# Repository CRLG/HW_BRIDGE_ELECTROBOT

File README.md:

# HW_BRIDGE_ELECTROBOT
Carte pont en H pour moteur DC

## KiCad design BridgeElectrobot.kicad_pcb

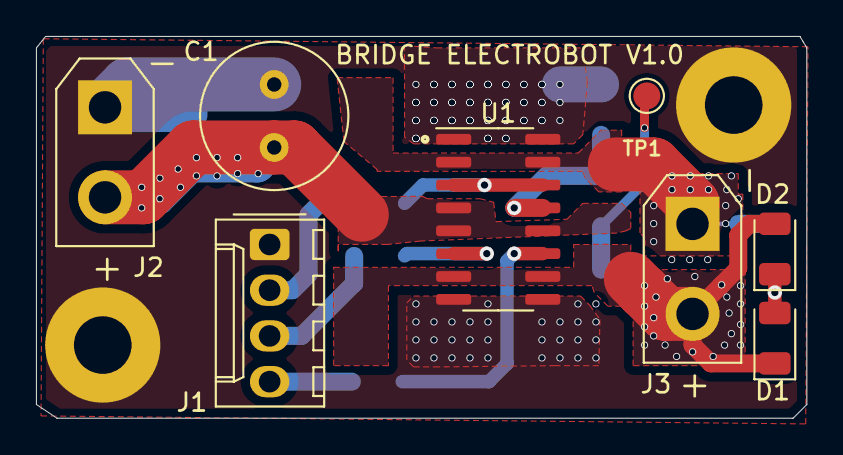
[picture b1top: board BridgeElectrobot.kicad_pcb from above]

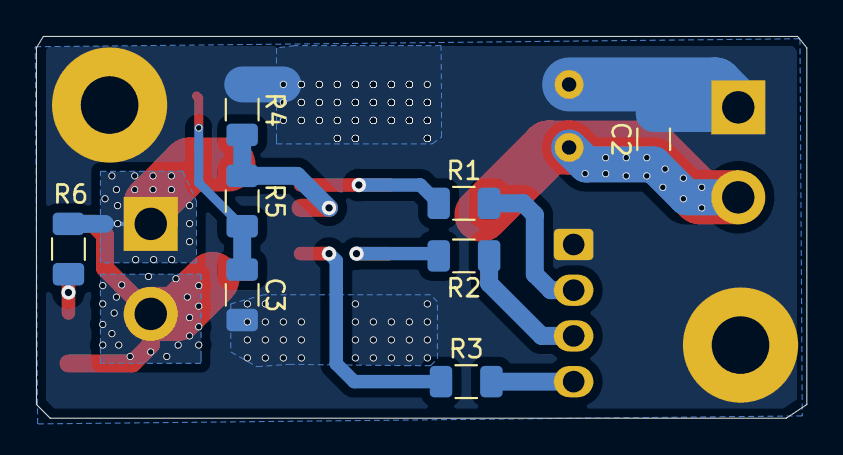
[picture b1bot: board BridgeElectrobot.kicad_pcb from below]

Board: 2 copper layers, 42.8 x 21.2 mm, 18 parts (8 on the bottom side), 13 nets.

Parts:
C1: 220u; C_Radial_D8.0mm_H11.5mm_P3.50mm
C2: 100n; C_1206_3216Metric
C3: 10n; C_1206_3216Metric
D1: VERTE; LED_1206_3216Metric
D2: ROUGE; LED_1206_3216Metric
H1, H2: MountingHole_Pad; MountingHole_3.2mm_M3_Pad
J1: Conn_01x04; Molex_KK-254_AE-6410-04A_1x04_P2.54mm_Vertical
J2: Conn_XT30M; AMASS_XT30UPB-M_1x02_P5.0mm_Vertical
J3: Conn_XT30F; AMASS_XT30UPB-F_1x02_P5.0mm_Vertical
R1, R2, R3: 1k; R_1206_3216Metric
R4: R; R_1206_3216Metric
R5: 10k; R_1206_3216Metric
R6: 4.7k; R_1206_3216Metric
TP1: TestPoint; TestPoint_Pad_D1.5mm
U1: VNH7070AS; SOIC-16_3.9x9.9mm_P1.27mm

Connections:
/INA: R1.1, U1.3, U1.14
/INB: R2.1, U1.6
/OUTA: J3.1, R6.2, U1.2, U1.15
/OUTB: D1.1, D2.2, J3.2, U1.7, U1.10
/PWM: R3.1, U1.11
/VCC: C1.1, C2.1, J2.2, U1.4, U1.5, U1.12
/_INA: J1.2, R1.2
/_INB: J1.3, R2.2
/_PWM: J1.4, R3.2
GND: C1.2, C2.2, C3.2, H1.1, H2.1, J1.1, J2.1, R4.1, U1.1, U1.8, U1.9, U1.16
unnamed: C3.1, R5.2, TP1.1
unnamed: D1.2, D2.1, R6.1
unnamed: R4.2, R5.1, U1.13

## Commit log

2019-12-21 Ajout du sous-module KICAD_LIB au projet
2019-12-23 Version initiale du schéma de la carte
2019-12-30 Ajout des références RS au schéma
2020-01-02 Version initiale du routage de la carte
2020-01-10 Modification footprint trou de fixation + ajout fichiers gerber
2020-08-26 Mise à jour pour bénéficier de la vue 3D des XT30
2020-08-28 Mise à jour version de KICAD_LIB
    Pour bénéficier de la présence des connecteurs XT30 dans l'export de la carte en .step
